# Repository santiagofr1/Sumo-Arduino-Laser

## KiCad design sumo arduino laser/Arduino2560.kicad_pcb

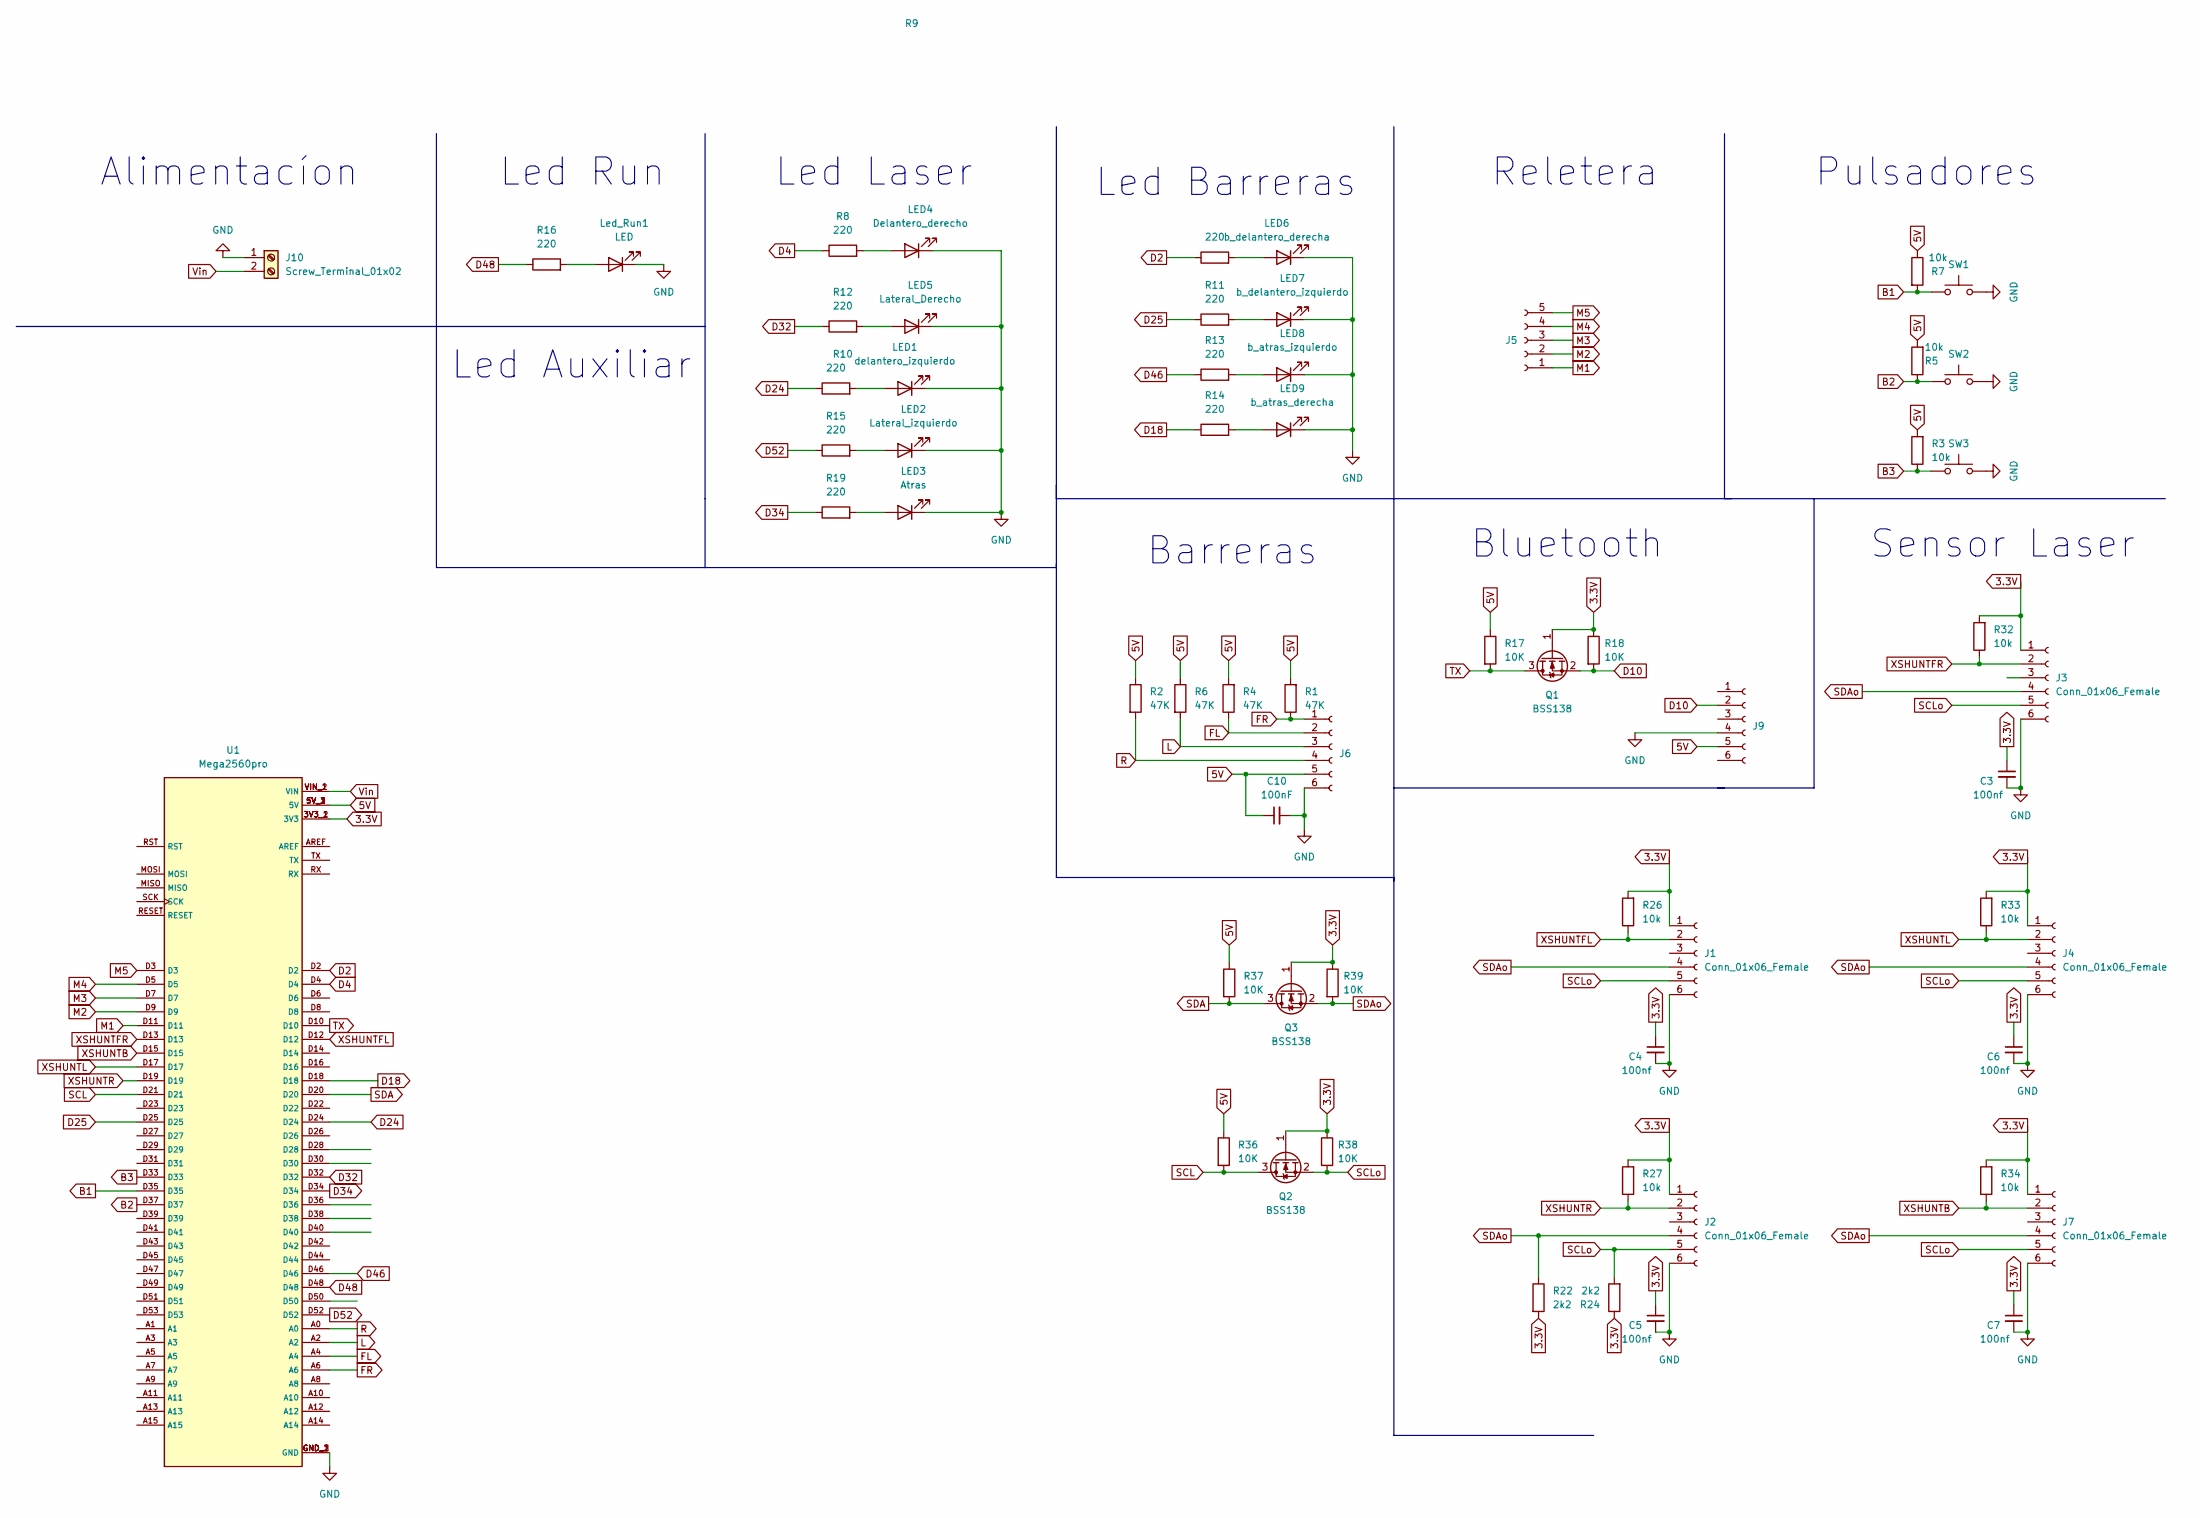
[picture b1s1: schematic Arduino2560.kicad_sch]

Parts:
C3, C4, C5, C6, C7: 100nf; C_0805_2012Metric_Pad1.18x1.45mm_HandSolder
C10: 100nF; C_0805_2012Metric_Pad1.18x1.45mm_HandSolder
J1, J2, J3, J4, J7, J9: Conn_01x06_Female; PinHeader_1x06_P2.54mm_Vertical
J5: Conn_01x05_Female; PinHeader_1x05_P2.54mm_Vertical
J6: Conn_01x06_Female; Molex_SL_171971-0006_1x06_P2.54mm_Vertical
J10: Screw_Terminal_01x02; TerminalBlock_MetzConnect_Type011_RT05502HBWC_1x02_P5.00mm_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
LED1: delantero_izquierdo; LED_D3.0mm
LED2: Lateral_izquierdo; LED_D3.0mm
LED3: Atras; LED_D3.0mm
LED4: Delantero_derecho; LED_D3.0mm
LED5: Lateral_Derecho; LED_D3.0mm
LED6: b_delantero_derecha; LED_D3.0mm
LED7: b_delantero_izquierdo; LED_D3.0mm
LED8: b_atras_izquierdo; LED_D3.0mm
LED9: b_atras_derecha; LED_D3.0mm
Led_Run1: LED; LED_D5.0mm
Q1, Q2, Q3: BSS138; SOT-23
R1, R2, R4, R6: 47K; R_0805_2012Metric_Pad1.20x1.40mm_HandSolder
R3, R5, R7, R26, R27, R32, R33, R34: 10k; R_0805_2012Metric_Pad1.20x1.40mm_HandSolder
R8, R9, R10, R11, R12, R13, R14, R15, R16, R19: 220; R_0805_2012Metric_Pad1.20x1.40mm_HandSolder
R17, R18, R36, R37, R38, R39: 10K; R_0805_2012Metric_Pad1.20x1.40mm_HandSolder
R22, R24: 2k2; R_0805_2012Metric_Pad1.20x1.40mm_HandSolder
SW1, SW2, SW3: .; SW_PUSH-12mm
U1: Mega2560pro

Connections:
3.3V: C3.1, C4.1, C5.1, C6.1, C7.1, J1.1, J2.1, J3.1, J4.1, J7.1, Q1.1 (G), Q2.1 (G), Q3.1 (G), R18.1, R22.2, R24.1, R26.2, R27.2, R32.2, R33.2, R34.2, R38.1, R39.1, U1.3V3_1 (3V3), U1.3V3_2 (3V3)
5V: C10.1, J6.5, J9.5, R1.2, R2.1, R3.2, R4.2, R5.2, R6.1, R7.1, R17.1, R36.1, R37.1, U1.5V_1 (5V), U1.5V_2 (5V), U1.5V_3 (5V)
B1: R7.2, SW1.1, U1.D35
B2: R5.1, SW2.1, U1.D37
B3: R3.1, SW3.1, U1.D33
D2: R9.1, U1.D2
D4: R8.1, U1.D4
D10: J9.2, Q1.2 (S), R18.2
D18: R14.1, U1.D18
D24: R10.1, U1.D24
D25: R11.1, U1.D25
D32: R12.1, U1.D32
D34: R19.1, U1.D34
D46: R13.1, U1.D46
D48: R16.1, U1.D48
D52: R15.1, U1.D52
FL: J6.2, R4.1, U1.A4
FR: J6.1, R1.1, U1.A6
GND: C3.2, C4.2, C5.2, C6.2, C7.2, C10.2, J1.6, J2.6, J3.6, J4.6, J6.6, J7.6, J9.4, J10.1, LED1.1 (K), LED2.1 (K), LED3.1 (K), LED4.1 (K), LED5.1 (K), LED6.1 (K), LED7.1 (K), LED8.1 (K), LED9.1 (K), Led_Run1.1 (K), SW1.2, SW2.2, SW3.2, U1.GND_1 (GND), U1.GND_2 (GND), U1.GND_3 (GND)
L: J6.3, R6.2, U1.A2
M1: J5.1, U1.D11
M2: J5.2, U1.D9
M3: J5.3, U1.D7
M4: J5.4, U1.D5
M5: J5.5, U1.D3
unnamed: LED1.2 (A), R10.2
unnamed: LED2.2 (A), R15.2
unnamed: LED3.2 (A), R19.2
unnamed: LED4.2 (A), R8.2
unnamed: LED5.2 (A), R12.2
unnamed: LED6.2 (A), R9.2
unnamed: LED7.2 (A), R11.2
unnamed: LED8.2 (A), R13.2
unnamed: LED9.2 (A), R14.2
unnamed: Led_Run1.2 (A), R16.2
R: J6.4, R2.2, U1.A0
SCL: Q2.3 (D), R36.2, U1.D21
SCLo: J1.5, J2.5, J3.5, J4.5, J7.5, Q2.2 (S), R24.2, R38.2
SDA: Q3.3 (D), R37.2, U1.D20
SDAo: J1.4, J2.4, J3.4, J4.4, J7.4, Q3.2 (S), R22.1, R39.2
TX: Q1.3 (D), R17.2, U1.D10
Vin: J10.2, U1.VIN_1 (VIN), U1.VIN_2 (VIN)
XSHUNTB: J7.2, R34.1, U1.D15
XSHUNTFL: J1.2, R26.1, U1.D12
XSHUNTFR: J3.2, R32.1, U1.D13
XSHUNTL: J4.2, R33.1, U1.D17
XSHUNTR: J2.2, R27.1, U1.D19

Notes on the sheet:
Reletera
Bluetooth
Led Run
Led Auxiliar
Led Laser
Sensor Laser
Alimentacíon
Barreras
Pulsadores
Led Barreras

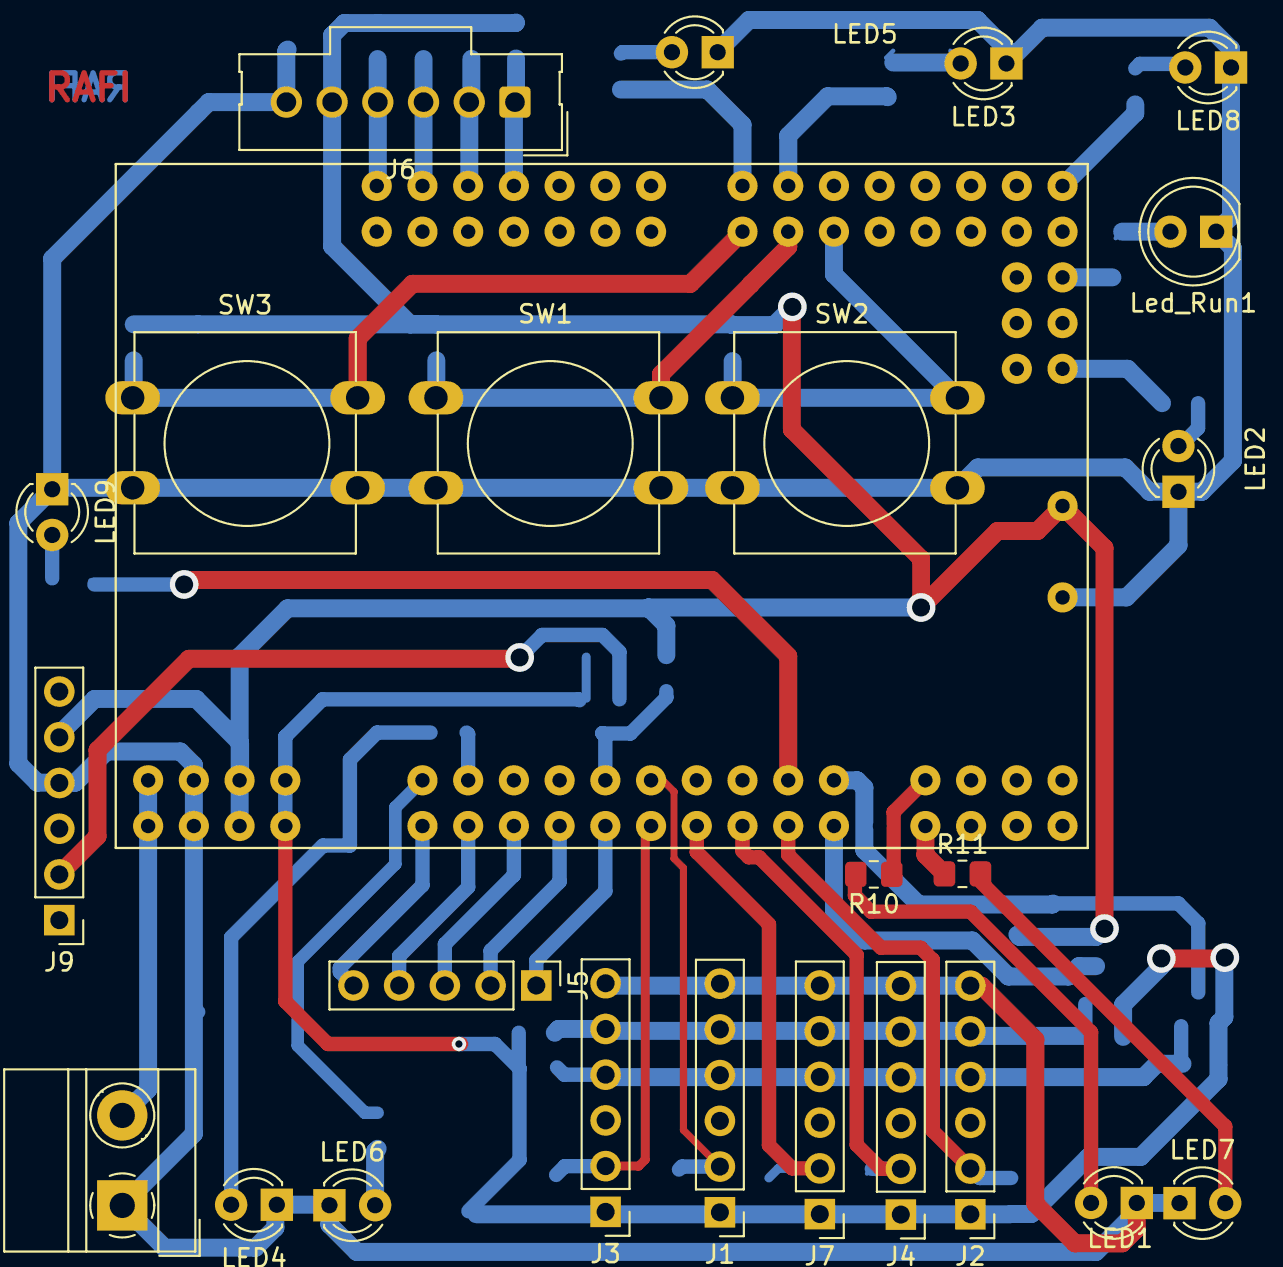
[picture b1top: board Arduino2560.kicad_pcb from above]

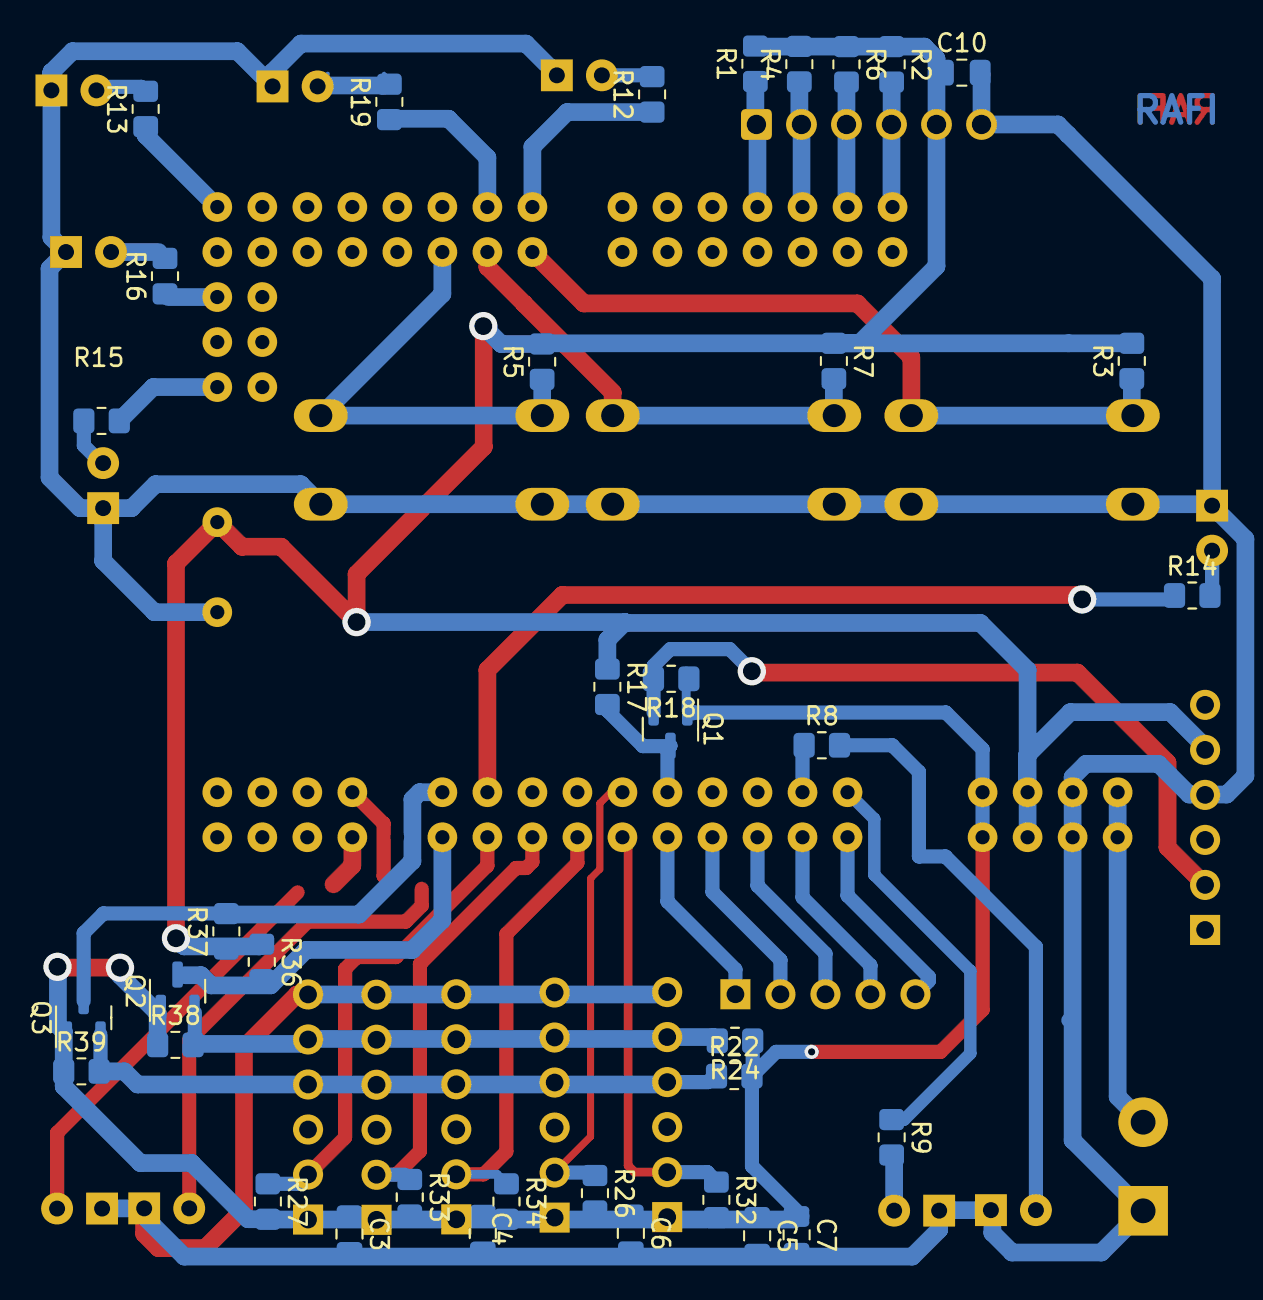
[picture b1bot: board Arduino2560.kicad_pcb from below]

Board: 2 copper layers, 62 parts (37 on the bottom side), 47 nets.
